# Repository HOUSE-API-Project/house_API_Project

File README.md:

#crontab edit main raspberry Pi 

in case at the /home/pi directory.

`git clone git@github.com:HOUSE-API-Project/house_API_Project.git`  
`crontab -e`

ant then

\* * * * * /usr/bin/ruby /home/pi/house_API_Project/wifi/wifi_3f.rb  
\* * * * * python /home/pi/ayafuji_work/house_API_Project/temperature/ds18b20.py  
\* * * * * /usr/bin/ruby /home/pi/ayafuji_work/house_API_Project/temperature/temperature.rb  
\* * * * * /usr/bin/ruby /home/pi/house_API_Project/wifi/wifi_1f.rb  
\* * * * * /usr/bin/ruby /home/pi/house_API_Project/wifi/wifi_2f.rb  
\* * * * * /usr/bin/ruby /home/pi/house_API_Project/wifi/wifi_bf.rb  
\* * * * * sudo python /home/pi/house_API_Project/humidity/humidity_dht22.py

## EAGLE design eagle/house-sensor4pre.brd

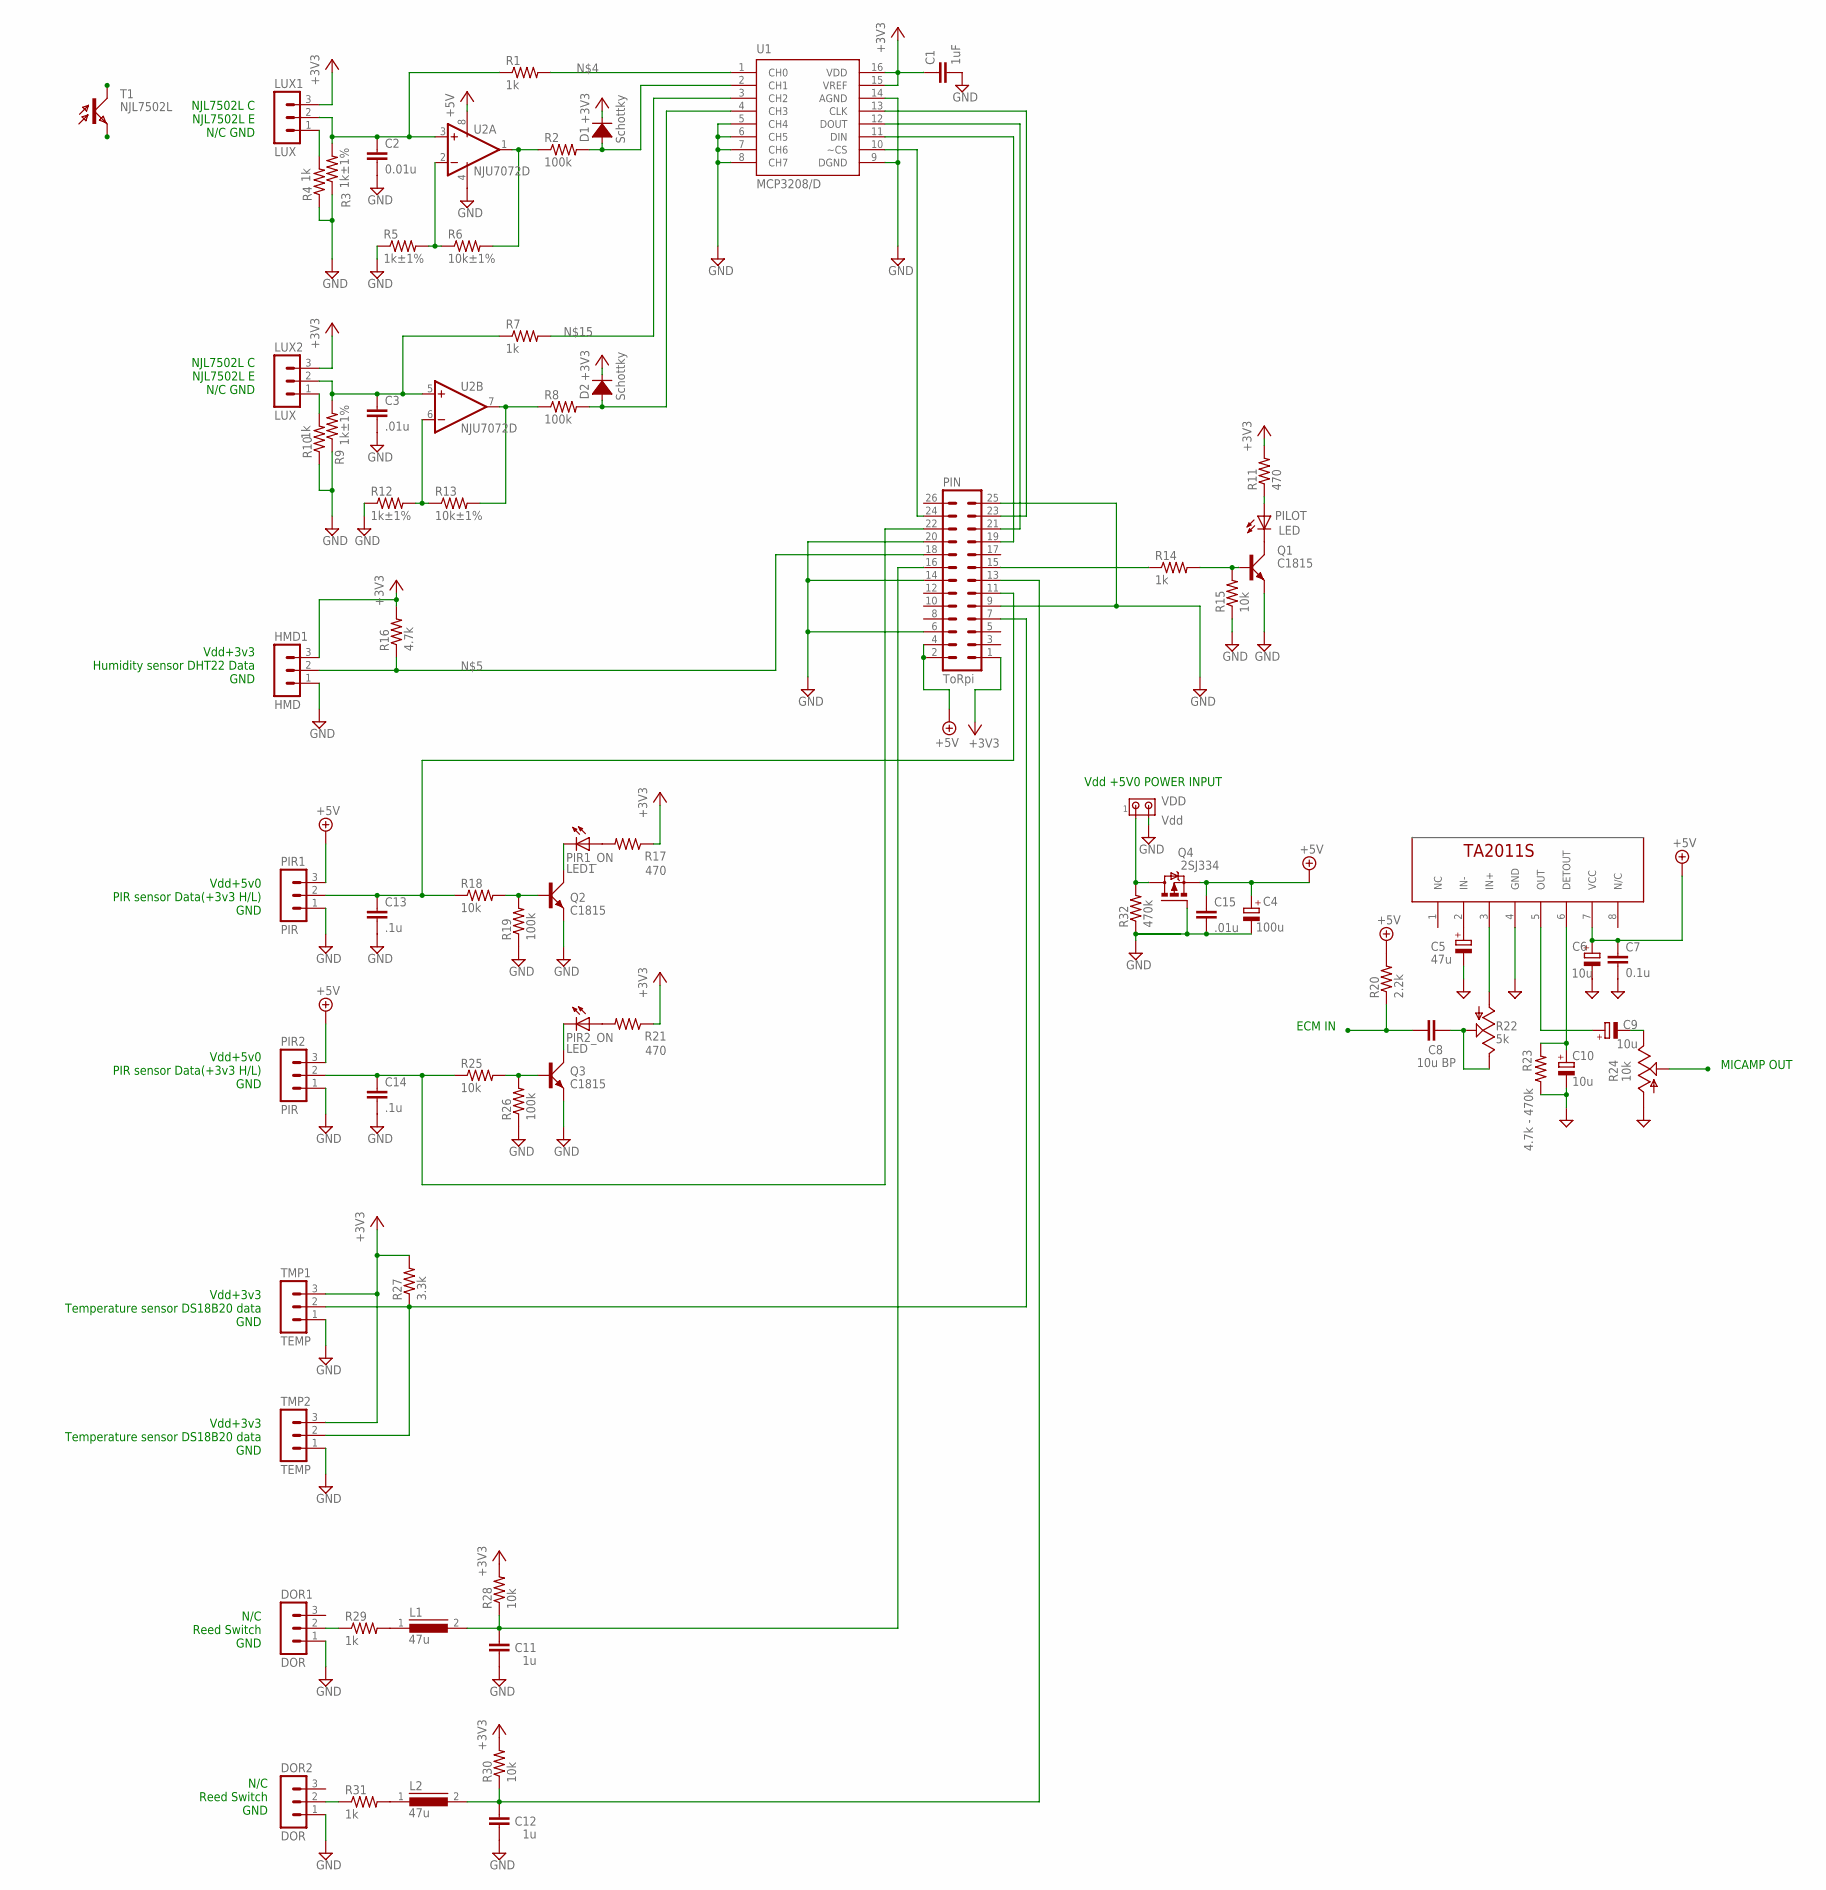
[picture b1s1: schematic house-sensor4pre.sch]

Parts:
C1: 1uF; C025-025X050
C2: 0.01u; C025-024X044
C3: .01u; C025-024X044
C4: 100u; E1,8-4
C5: 47u; E1,8-4
C6, C9, C10: 10u; E1,8-4
C7: 0.1u; C025-024X044
C8: 10u BP; C025-024X044
C11, C12: 1u; C050-024X044
C13, C14: .1u; C025-030X050
C15: .01u; C025-025X050
D1, D2: Schottky; DIODE_V
DOR1, DOR2: DOR; MA03-1
HMD1: HMD; MA03-1
L1, L2: 47u; LBC-SE
LUX1, LUX2: LUX; MA03-1
PILOT: LED; LED_LD260
PIN: ToRpi; MA13-2
PIR1, PIR2: PIR; MA03-1
PIR1_ON: LED1; LED_LD260
PIR2_ON: LED; LED_LD260
Q1, Q2, Q3: C1815; TO92-LINE
R1, R7: 1k; 0207/2V
R2: 100k; 0207/10
R3, R5, R9, R12: 1k±1%; 0207/2V
R4, R10: 1k; 0309V
R6, R13: 10k±1%; 0207/2V
R8: 100k; 0204/7
R11: 470; 0207/2V
R14: 1k; 0204V
R15: 10k; 0207/2V
R16: 4.7k; 0207/2V
R17, R21: 470; 0204V
R18, R25, R28, R30: 10k; 0204V
R19, R26: 100k; 0204V
R20: 2.2k; 0207/2V
R22: 5k; B25P
R23: 4.7k - 470k; 0207/2V
R24: 10k; B25P
R27: 3.3k; 0204V
R29, R31: 1k; 0207/5V
R32: 470k; 0204V
T1: NJL7502L; BPX81
TMP1, TMP2: TEMP; MA03-1
U1: MCP3208/D; DIL16
U2: NJU7072D; DIL08
U$1: TA2011S; SIP8
VDD: Vdd; 10X02MTA

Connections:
+3V3: C1.1, D1.P$2 (K), D2.P$2 (K), HMD1.3, LUX1.3, LUX2.3, PIN.1, R11.2, R16.2, R17.1, R21.1, R27.2, R28.2, R30.2, TMP1.3, TMP2.3, U1.15 (VREF), U1.16 (VDD)
+5V: C4.+, C6.+, C7.1, C15.1, PIN.2, PIN.4, PIR1.3, PIR2.3, R20.2, U2.8 (V+), U$1.7 (VCC)
GND: C1.2, C2.2, C3.2, C4.-, C5.-, C6.-, C7.2, C10.-, C11.1, C12.1, C13.2, C14.2, C15.2, DOR1.1, DOR2.1, HMD1.1, PIN.6, PIN.9, PIN.14, PIN.20, PIN.25, PIR1.1, PIR2.1, Q1.3 (E), Q2.3 (E), Q3.3 (E), R3.1, R4.1, R5.1, R9.1, R10.1, R12.1, R15.1, R19.1, R23.1, R24.A, R26.1, R32.1, TMP1.1, TMP2.1, U1.5 (CH4), U1.6 (CH5), U1.7 (CH6), U1.8 (CH7), U1.9 (DGND), U1.14 (AGND), U2.4 (V-), U$1.4 (GND), VDD.2
unnamed: C2.1, LUX1.2, R1.1, R3.2, U2.3 (+IN)
unnamed: R5.2, R6.1, U2.2 (-IN)
unnamed: R2.1, R6.2, U2.1 (OUT)
unnamed: R1.2, U1.1 (CH0)
unnamed: HMD1.2, PIN.18, R16.1
unnamed: PIN.23, U1.13 (CLK)
unnamed: D1.P$1 (A), R2.2, U1.2 (CH1)
unnamed: PIN.21, U1.12 (DOUT)
unnamed: PIN.19, U1.11 (DIN)
unnamed: R12.2, R13.1, U2.6 (-IN)
unnamed: R8.1, R13.2, U2.7 (OUT)
unnamed: C3.1, LUX2.2, R7.1, R9.2, U2.5 (+IN)
unnamed: PIN.24, U1.10 (~CS)
unnamed: D2.P$1 (A), R8.2, U1.4 (CH3)
unnamed: R7.2, U1.3 (CH2)
unnamed: Q1.1 (B), R14.2, R15.2
unnamed: C13.1, PIN.11, PIR1.2, R18.1
unnamed: Q2.1 (B), R18.2, R19.2
unnamed: PIR1_ON.K (C), Q2.2 (C)
unnamed: PIR1_ON.A, R17.2
unnamed: C14.1, PIN.22, PIR2.2, R25.1
unnamed: Q3.1 (B), R25.2, R26.2
unnamed: PIR2_ON.K (C), Q3.2 (C)
unnamed: PIR2_ON.A, R21.2
unnamed: PILOT.K (C), Q1.2 (C)
unnamed: PILOT.A, R11.1
unnamed: PIN.7, R27.1, TMP1.2, TMP2.2
unnamed: C12.2, L2.2, PIN.13, R30.1
unnamed: R22.A, U$1.3 (IN+)
unnamed: PIN.15, R14.1
unnamed: L1.1, R29.2
unnamed: DOR1.2, R29.1
unnamed: L2.1, R31.2
unnamed: DOR2.2, R31.1
unnamed: C11.2, L1.2, PIN.16, R28.1
unnamed: C9.+, U$1.5 (OUT)
unnamed: C9.-, R24.E
unnamed: LUX1.1, R4.2
unnamed: LUX2.1, R10.2
unnamed: C8.2, R22.E, R22.S
unnamed: C8.1, R20.1
unnamed: C10.+, R23.2, U$1.6 (DETOUT)
unnamed: C5.+, U$1.2 (IN-)
unnamed: R32.2, VDD.1

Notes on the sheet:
NJL7502L C NJL7502L E N/C GND
Vdd+3v3 Humidity sensor DHT22 Data GND
Vdd+5v0 PIR sensor Data(+3v3 H/L) GND
Vdd+3v3 Temperature sensor DS18B20 data GND
N/C Reed Switch GND
ECM IN
MICAMP OUT
Vdd +5V0 POWER INPUT

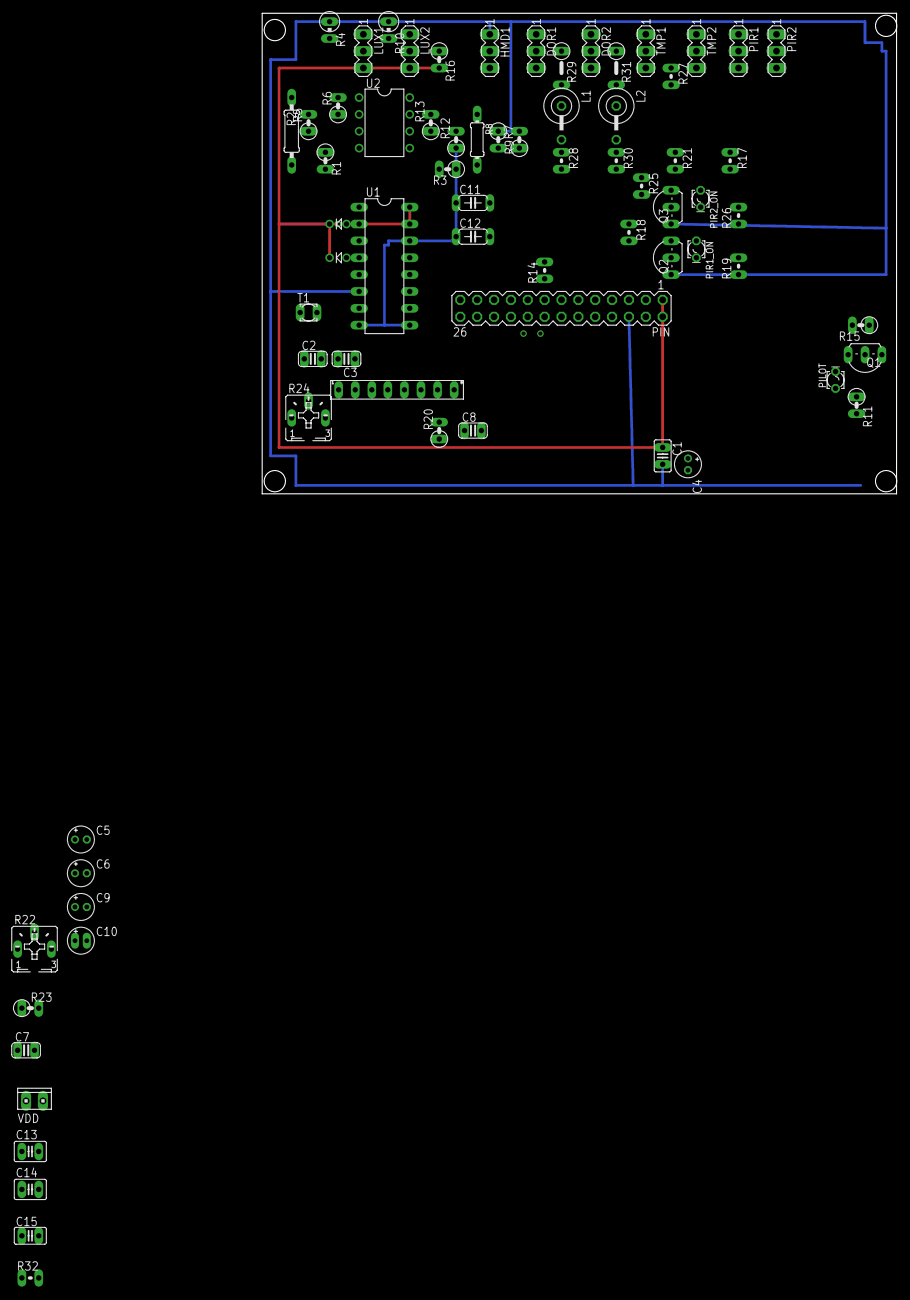
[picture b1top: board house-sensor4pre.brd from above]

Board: 2 copper layers, 95.6 x 72.4 mm, 72 parts (0 on the bottom side), 47 nets.

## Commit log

2013-07-10 add humancounter prototype
2013-07-10 add temperature sensor reader prototype
2013-07-10 .gitignore
    .gitignore
2013-07-10 clean
2013-07-11 add comment about sensors
2013-07-17 noise-level-meter
2013-08-13 add schematic draft
2013-08-13 add wifi
2013-08-13 Revert "merge clients codes"
    This reverts commit d72ac9911742e963d7bab19c4cc96d70a6700c22.
2013-08-13 minor changes
2013-09-15 abstraction
2013-09-15 a little changes
    rm .ds_store & rm emacs backup file
2013-11-03 add value community password
2013-11-03 add value wifi_community_password
2013-11-15 add wifi codes
2013-11-15 add humidity tracking code
2013-12-17 change some constant
2014-01-03 fix post_url
2014-01-03 crontab -e
2014-01-03 edit crontab
2014-01-03 same
